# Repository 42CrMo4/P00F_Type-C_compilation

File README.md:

# Type-C compilation

Compilation of USB Type-C connectors

### Goal

The goal of the project will be:
- [ ] **undefined** - not known what the project will bring 
- [ ] **learn** - personally learn something new, no usefull outcome expected
- [x] **prototype** - a working prototype or mvp
- [ ] **80-20-rule** - 80% outcome with 20% effort
- [ ] **Product** - lets see :wink:

## Description. 

| Font                                                                    | Back                                                                      |
|-------------------------------------------------------------------------|---------------------------------------------------------------------------|
|  |  |

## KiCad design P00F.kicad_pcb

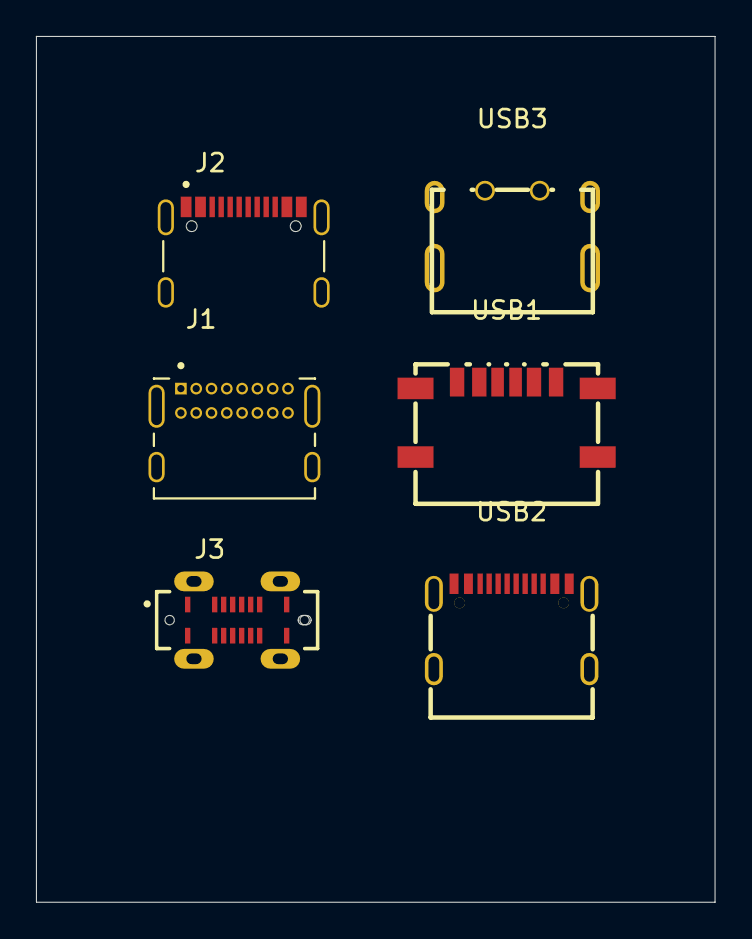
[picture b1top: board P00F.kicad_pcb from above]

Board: 2 copper layers, 37.7 x 48.1 mm, 6 parts (0 on the bottom side), 10 nets, no tracks yet.

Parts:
J1: UJ20-C-H-G-SMT-TR; UJ20-C-H-G-SMT-TR_CUI_UJ20-C-H-G-SMT-TR
J2: TYPE-C-31-M-12; TYPE-C-31-M-12_HRO_TYPE-C-31-M-12
J3: USB4120-03-C_REVA; USB4120-03-C_REVA_GCT_USB4120-03-C_REVA
USB1: TYPE-C-31-M-29; easyeda2kicad_USB-C-SMD_TYPE-C-31-M-29
USB2: TYPE-C-31-M-31; easyeda2kicad_USB-C-SMD_TYPE-C-31-M-31
USB3: TYPE-C-31-M-33; easyeda2kicad_USB-C-TH_TYPE-C-31-M-33

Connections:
unnamed: J1.A1 (GND), J1.A12 (GND), J1.B1 (GND), J1.B12 (GND)
unnamed: J1.SH1 (SHIELD), J1.SH2 (SHIELD), J1.SH3 (SHIELD), J1.SH4 (SHIELD)
unnamed: J1.A4 (VBUS), J1.A9 (VBUS), J1.B4 (VBUS), J1.B9 (VBUS)
unnamed: J2.A1_B12 (GND), J2.B1_A12 (GND)
unnamed: J2.A4_B9 (VBUS), J2.B4_A9 (VBUS)
unnamed: J3.A1 (GND_A), J3.A12 (GND_A)
unnamed: J3.B1 (GND_B), J3.B12 (GND_B)
unnamed: J3.S1 (SHIELD), J3.S2 (SHIELD), J3.S3 (SHIELD), J3.S4 (SHIELD)
unnamed: J3.A4 (VBUS_A), J3.A9 (VBUS_A)
unnamed: J3.B4 (VBUS_B), J3.B9 (VBUS_B)

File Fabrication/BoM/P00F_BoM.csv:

Row,Description,Part,References,Value,Footprint,Quantity Per PCB,Status,Datasheet,LCSC Part,MF,MAXIMUM_PACKAGE_HEIGHT,Package,Price,Check_prices,STANDARD,PARTREV,SnapEDA_Link,MP,Purchase-URL,Description_1,CUI_purchase_URL,Availability,MANUFACTURER,SNAPEDA_PN
1,,TYPE-C-31-M-12,J2,TYPE-C-31-M-12,TYPE-C-31-M-12_HRO_TYPE-C-31-M-12,1, ,,,"HRO Electronics Co., Ltd.",3.26 mm,Package,None,https://www.snapeda.com/parts/TYPE-C-31-M-12/HRO+Electronics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,Manufacturer Recommendations,2020.12.08,https://www.snapeda.com/parts/TYPE-C-31-M-12/HRO+Electronics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,TYPE-C-31-M-12,,USB Connectors 24 Receptacle 1 8.94*7.3mm RoHS,,Not in stock,"HRO Electronics Co., Ltd.",TYPE-C-31-M-12
2,,UJ20-C-H-G-SMT-TR,J1,UJ20-C-H-G-SMT-TR,UJ20-C-H-G-SMT-TR_CUI_UJ20-C-H-G-SMT-TR,1, ,,,CUI Devices,3.66mm,None,None,https://www.snapeda.com/parts/UJ20-C-H-G-SMT-TR/Same+Sky/vie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,Manufacturer Recommendations,1.01,https://www.snapeda.com/parts/UJ20-C-H-G-SMT-TR/Same+Sky/vie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,UJ20-C-H-G-SMT-TR,https://www.snapeda.com/api/url_track_click_mouser/?unipart_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 Devices&part_name=UJ20-C-H-G-SMT-TR&search_term=uj20-c-h-g-smt-tr,"Type C, USB 2.0, 480 Mbps, 20 Vdc, 5 A, Right Angle, Gold Flash, Surface Mount, Black Insulator, USB Receptacle",https://www.cuidevices.com/product/interconnect/connectors/u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,In Stock,CUI Devices,
3,,USB4120-03-C_REVA,J3,USB4120-03-C_REVA,USB4120-03-C_REVA_GCT_USB4120-03-C_REVA,1, ,,,Global Connector Technology,6.5mm,None,None,https://www.snapeda.com/parts/USB4120-03-C/Global+Connector+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,Manufacturer Recommendations,A,https://www.snapeda.com/parts/USB4120-03-C/Global+Connector+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,USB4120-03-C,,"USB 2.0 Connector Type C Vertical Receptacle, 6.50mm profile, 16 Pins, Surface mount, Top mount, low profile, low cost",,In Stock,GCT,
4,,TYPE-C-31-M-29,USB1,TYPE-C-31-M-29,easyeda2kicad_USB-C-SMD_TYPE-C-31-M-29,1, ,,C2689969,,,,,,,,,,,,,,,
5,,TYPE-C-31-M-31,USB2,TYPE-C-31-M-31,easyeda2kicad_USB-C-SMD_TYPE-C-31-M-31,1, ,,C2760486,,,,,,,,,,,,,,,
6,,TYPE-C-31-M-33,USB3,TYPE-C-31-M-33,easyeda2kicad_USB-C-TH_TYPE-C-31-M-33,1, ,,C2848624,,,,,,,,,,,,,,,

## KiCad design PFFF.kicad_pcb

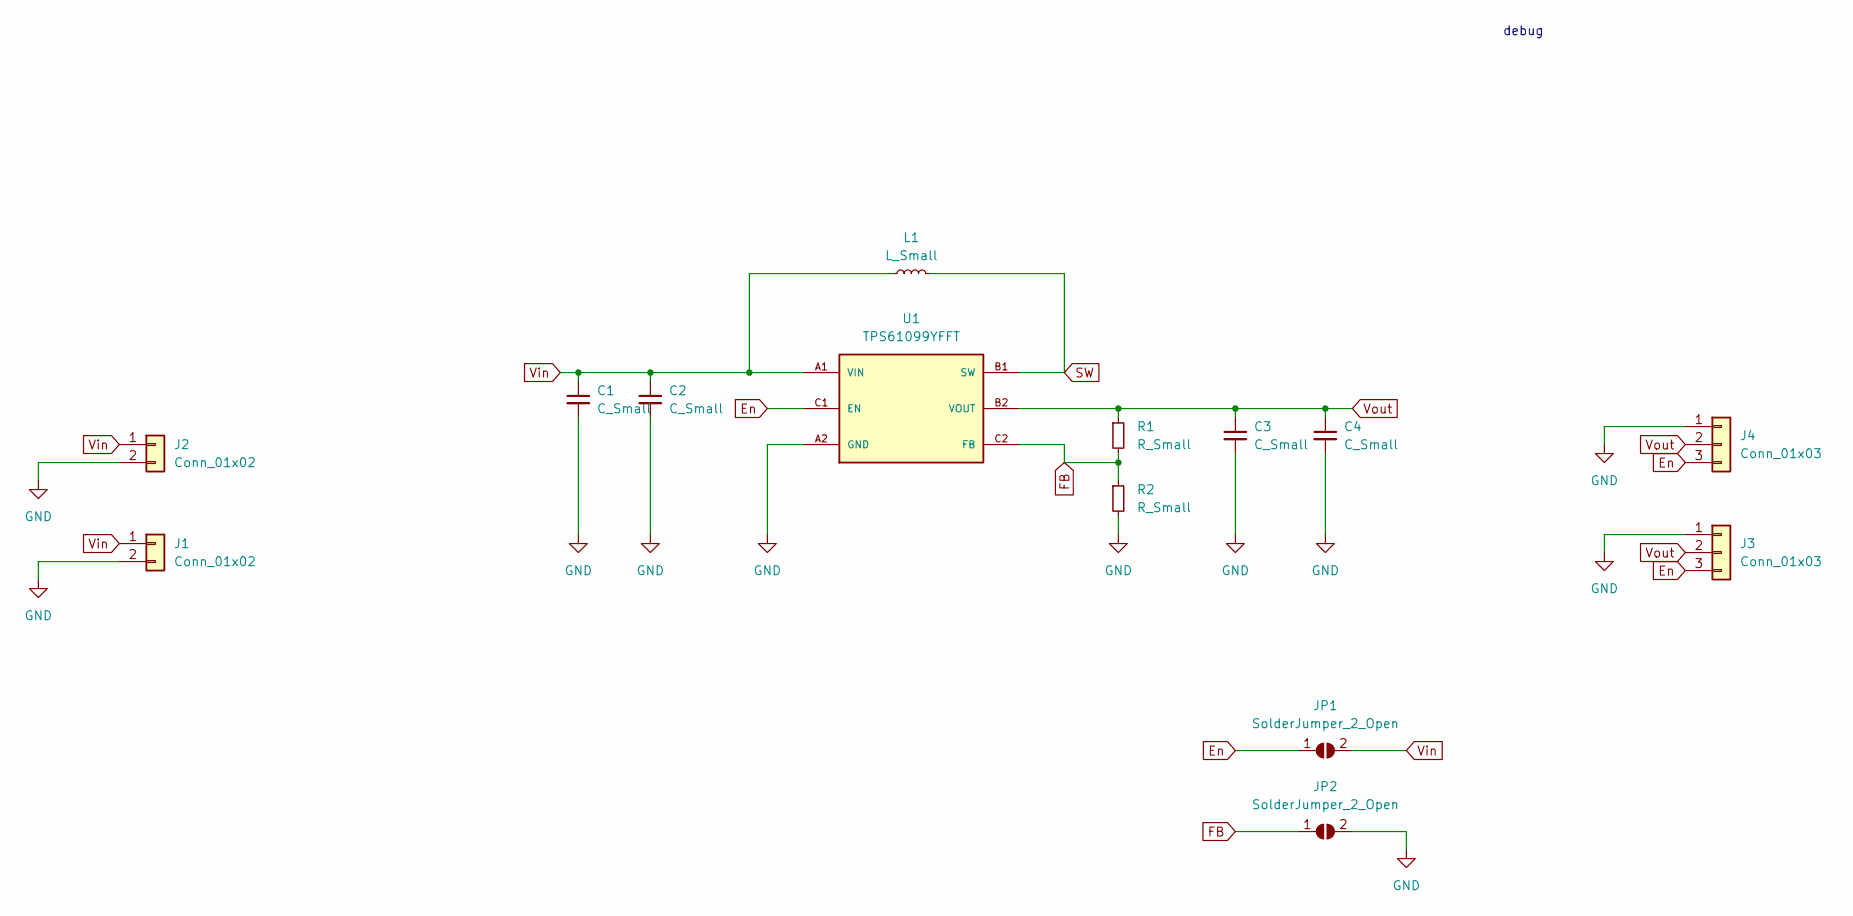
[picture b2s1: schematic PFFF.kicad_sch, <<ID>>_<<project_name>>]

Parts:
C1, C2, C3, C4: C_Small; C_0805_2012Metric
J1, J2: Conn_01x02; PinHeader_1x02_P2.54mm_Vertical
J3, J4: Conn_01x03; PinHeader_1x03_P2.54mm_Vertical
JP1, JP2: SolderJumper_2_Open; SolderJumper-2_P1.3mm_Open_RoundedPad1.0x1.5mm
L1: L_Small; L_1008_2520Metric
R1, R2: R_Small; R_0805_2012Metric
U1: TPS61099YFFT; BGA6N40P3X2_122X88X62N; PARTREV K

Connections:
En: J3.3, J4.3, JP1.1 (A), U1.C1 (EN)
FB: JP2.1 (A), R1.2, R2.1, U1.C2 (FB)
GND: C1.2, C2.2, C3.2, C4.2, J1.2, J2.2, J3.1, J4.1, JP2.2 (B), R2.2, U1.A2 (GND)
SW: L1.2, U1.B1 (SW)
Vin: C1.1, C2.1, J1.1, J2.1, JP1.2 (B), L1.1, U1.A1 (VIN)
Vout: C3.1, C4.1, J3.2, J4.2, R1.1, U1.B2 (VOUT)

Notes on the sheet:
debug

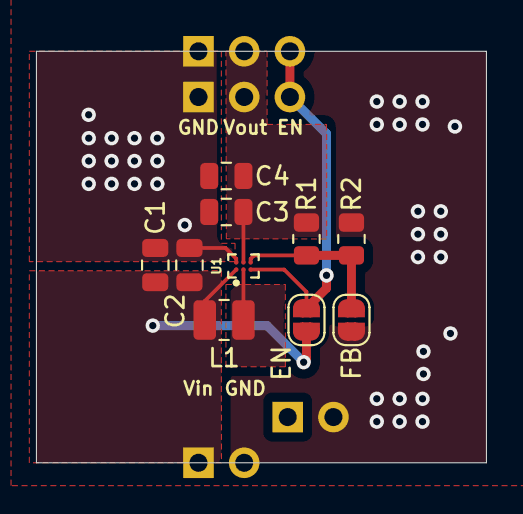
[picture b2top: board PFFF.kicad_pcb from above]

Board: 2 copper layers, 25.0 x 22.9 mm, 14 parts (0 on the bottom side), 6 nets.

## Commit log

2024-11-04 update to latest template v8
2024-11-04 add array check
2024-11-04 fake change
2024-11-04 add all USB Type-C
2024-11-04 rename files
2024-11-04 add and remove 3d Files
2024-11-04 Update Bom and PCB_top
2025-02-22 update to KiCad v9
2025-02-22 use kicad9_auto_full dev
    no github action yet for kicad 9
